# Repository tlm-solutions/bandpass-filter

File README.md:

# Bandpass filter for the SDR

PCB is designed for JLCPCB 4 layer impedance controlled JLC04161H-7628 1.6mm thickness 1oz outer copper 0.5oz inner copper

## Measurements of the first prototype

| Gain   | Frequency |
|--------|-----------|
| -3dB   | 162MHz    |
| 14.2dB | 170.8MHz  |
| -3dB   | 183MHz    |

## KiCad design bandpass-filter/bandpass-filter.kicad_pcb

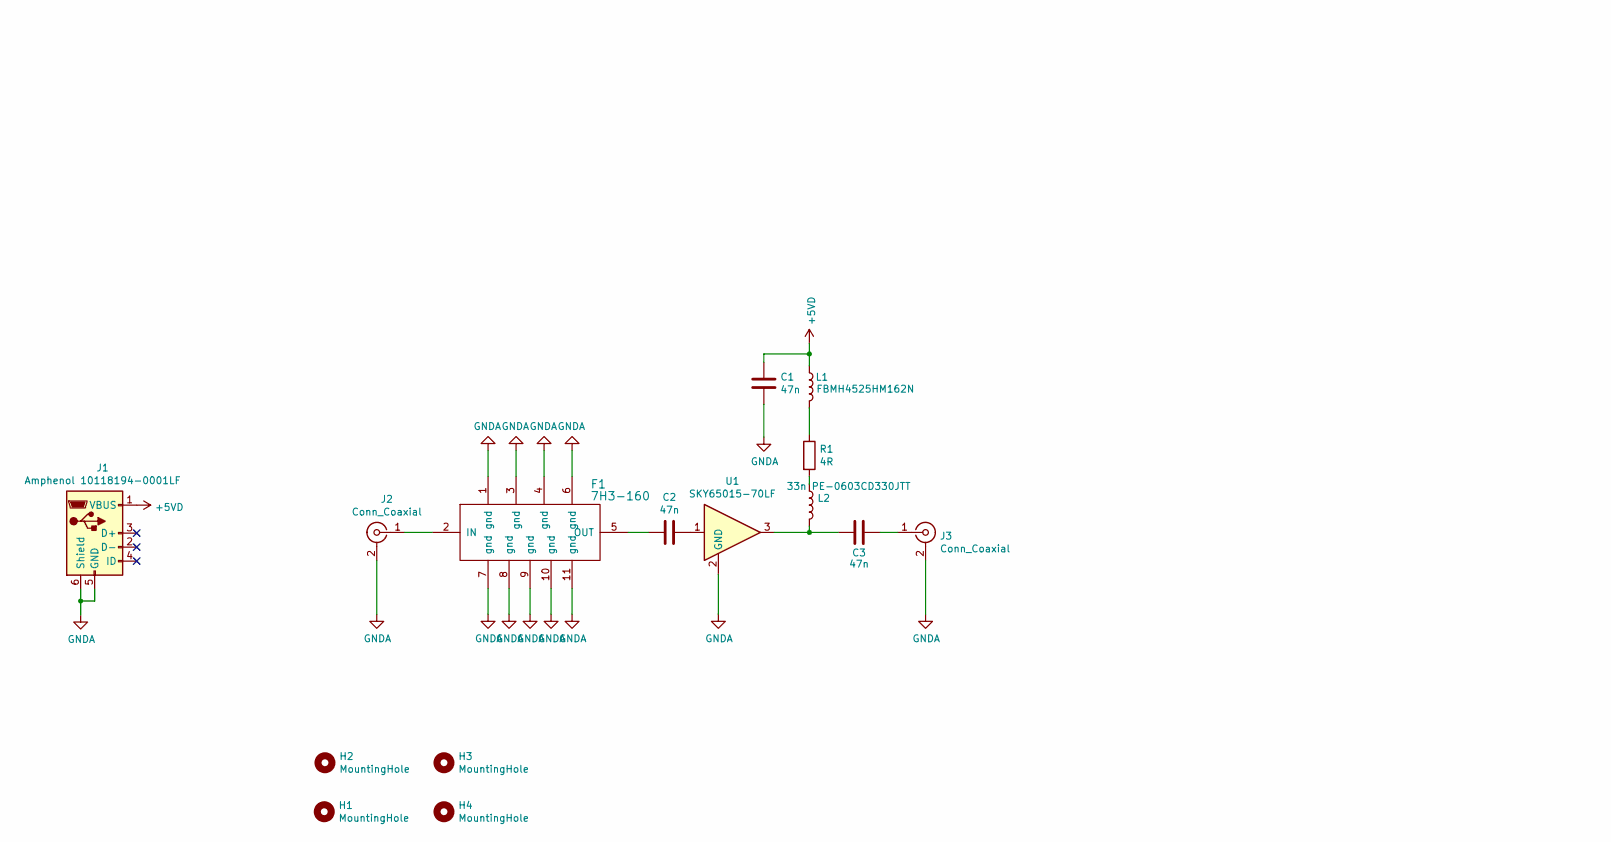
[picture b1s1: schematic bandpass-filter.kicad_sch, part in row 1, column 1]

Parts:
C1, C2, C3: 47n; C_0603_1608Metric_Pad1.08x0.95mm_HandSolder
F1: 7H3-160; 7h3
H1, H2, H3, H4: MountingHole; MountingHole_4.3mm_M4
J1: Amphenol 10118194-0001LF; USB_Micro-B_Amphenol_10118194_Horizontal
J2, J3: Conn_Coaxial; sma_connector
L1: FBMH4525HM162N; L_1812_4532Metric_Pad1.30x3.40mm_HandSolder
L2: 33n PE-0603CD330JTT; L_0603_1608Metric_Pad1.05x0.95mm_HandSolder
R1: 4R; R_0805_2012Metric_Pad1.20x1.40mm_HandSolder
U1: SKY65015-70LF; SOT-89-3_Handsoldering

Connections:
+5VD: C1.1, J1.1 (VBUS), L1.1
GNDA: C1.2, F1.1 (gnd), F1.3 (gnd), F1.4 (gnd), F1.6 (gnd), F1.7 (gnd), F1.8 (gnd), F1.9 (gnd), F1.10 (gnd), F1.11 (gnd), J1.5 (GND), J1.6 (Shield), J2.2 (Ext), J3.2 (Ext), U1.2 (GND)
unnamed: C2.1, U1.1
unnamed: C2.2, F1.5 (OUT)
unnamed: C3.1, J3.1 (In)
unnamed: C3.2, L2.2, U1.3
unnamed: F1.2 (IN), J2.1 (In)
unnamed: L1.2, R1.1
unnamed: L2.1, R1.2

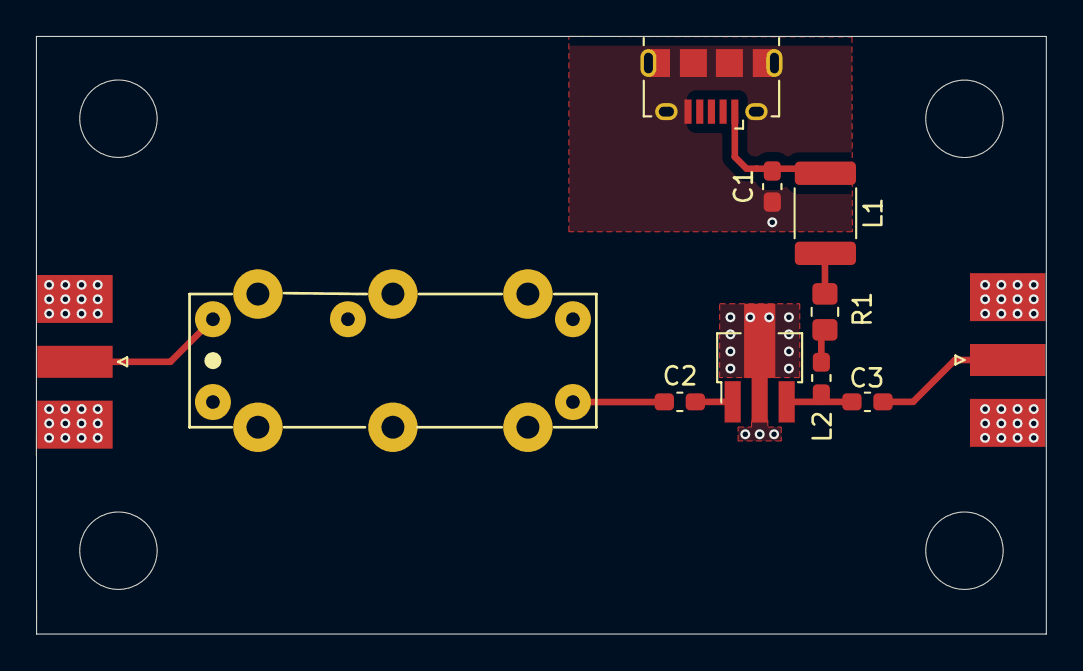
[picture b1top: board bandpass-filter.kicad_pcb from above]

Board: 4 copper layers, 56.1 x 33.2 mm, 15 parts (0 on the bottom side), 9 nets.

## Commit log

2022-06-25 remove todos
2022-07-13 Add rendering
2023-07-04 Update PCB with controlled impedance JLCPCB process. Change filter and amplifier order
